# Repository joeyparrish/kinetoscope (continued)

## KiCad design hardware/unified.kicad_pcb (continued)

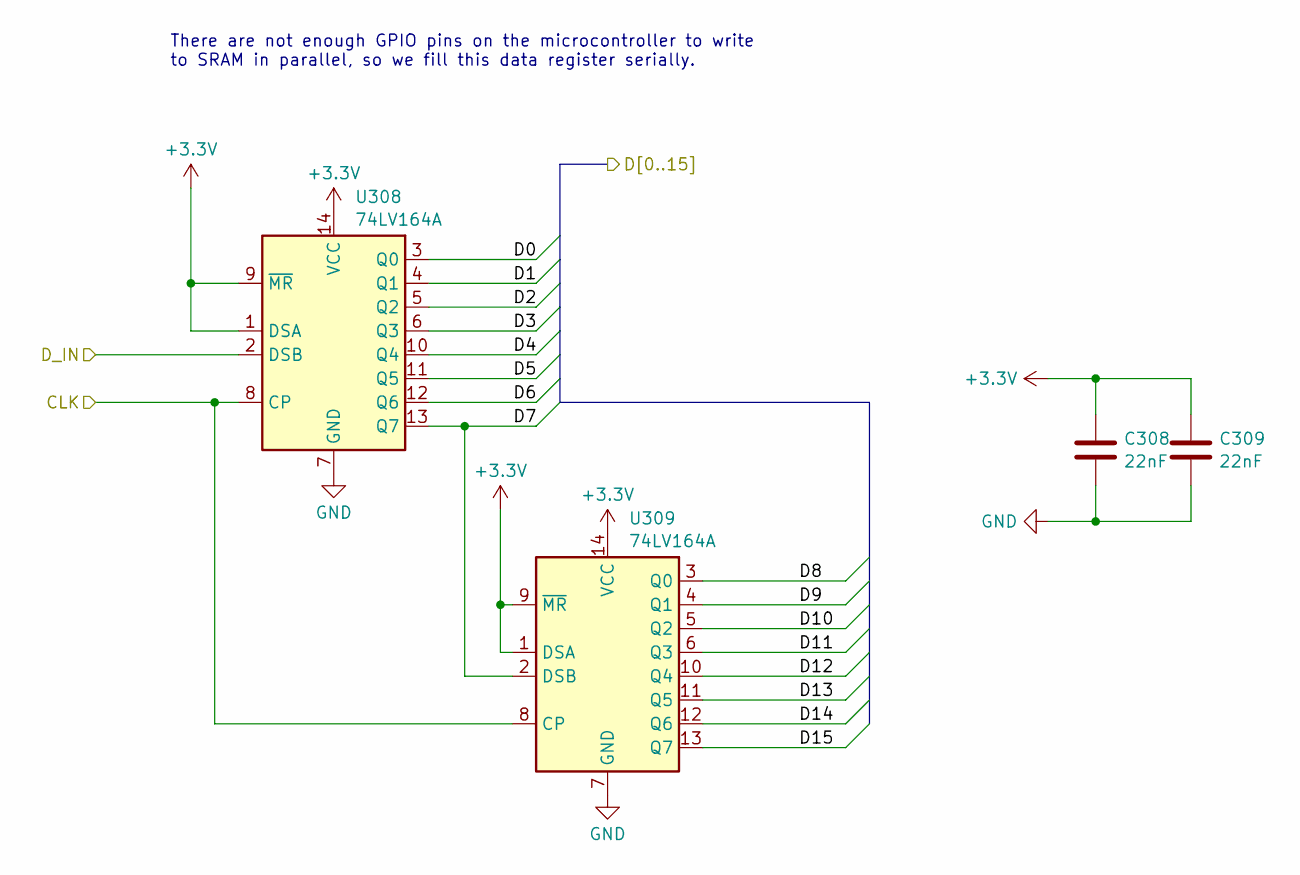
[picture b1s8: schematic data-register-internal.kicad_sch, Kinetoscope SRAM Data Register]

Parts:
C308, C309: 22nF; C_0603_1608Metric; Mouser Part Number 187-CL10B223KB8NNNC
U308, U309: 74LV164A; TSSOP-14_4.4x5mm_P0.65mm; Mouser Part Number 595-SN74LV164APWR

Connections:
+3.3V: C308.1, C309.1, U308.1 (DSA), U308.9 (~MR), U308.14 (VCC), U309.1 (DSA), U309.9 (~MR), U309.14 (VCC); also elsewhere on the board
GND: C308.2, C309.2, U308.7 (GND), U309.7 (GND); also elsewhere on the board
SRAM_D_CLK: U308.8 (CP), U309.8 (CP); also elsewhere on the board
SRAM_D_IN0: U308.3 (Q0); also elsewhere on the board
SRAM_D_IN1: U308.4 (Q1); also elsewhere on the board
SRAM_D_IN2: U308.5 (Q2); also elsewhere on the board
SRAM_D_IN3: U308.6 (Q3); also elsewhere on the board
SRAM_D_IN4: U308.10 (Q4); also elsewhere on the board
SRAM_D_IN5: U308.11 (Q5); also elsewhere on the board
SRAM_D_IN6: U308.12 (Q6); also elsewhere on the board
SRAM_D_IN7: U308.13 (Q7), U309.2 (DSB); also elsewhere on the board
SRAM_D_IN8: U309.3 (Q0); also elsewhere on the board
SRAM_D_IN9: U309.4 (Q1); also elsewhere on the board
SRAM_D_IN10: U309.5 (Q2); also elsewhere on the board
SRAM_D_IN11: U309.6 (Q3); also elsewhere on the board
SRAM_D_IN12: U309.10 (Q4); also elsewhere on the board
SRAM_D_IN13: U309.11 (Q5); also elsewhere on the board
SRAM_D_IN14: U309.12 (Q6); also elsewhere on the board
SRAM_D_IN15: U309.13 (Q7); also elsewhere on the board
SRAM_D_NEXT: U308.2 (DSB); also elsewhere on the board

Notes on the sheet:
There are not enough GPIO pins on the microcontroller to write to SRAM in parallel, so we fill this data register serially.

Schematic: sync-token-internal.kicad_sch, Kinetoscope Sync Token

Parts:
C310, C311: 22nF; C_0603_1608Metric; Mouser Part Number 187-CL10B223KB8NNNC
U310: 74AHC74; TSSOP-14_4.4x5mm_P0.65mm; Mouser Part Number 595-SN74AHC74PWR
U311: 74LVC2G125; VSSOP-8_2.3x2mm_P0.5mm; Mouser Part Number 771-LVC2G125DC125; JLCPCB Part Number C548582

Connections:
+3.3V: C310.1, C311.1, U310.14 (VCC), U311.8 (VCC); also elsewhere on the board
/microcontroller-internal/CMD_3V: U310.5 (Q), U311.2; also elsewhere on the board
/microcontroller-internal/ERR_3V: U310.9 (Q), U311.5; also elsewhere on the board
/microcontroller-internal/~CMD_CLR: U310.1 (~R); also elsewhere on the board
/microcontroller-internal/~CMD_OE: U311.1; also elsewhere on the board
/microcontroller-internal/~CMD_SET: U310.4 (~S); also elsewhere on the board
/microcontroller-internal/~ERR_CLR: U310.13 (~R); also elsewhere on the board
/microcontroller-internal/~ERR_OE: U311.7; also elsewhere on the board
/microcontroller-internal/~ERR_SET: U310.10 (~S); also elsewhere on the board
GND: C310.2, C311.2, U310.2 (D), U310.3 (C), U310.7 (GND), U310.11 (C), U310.12 (D), U311.4 (GND); also elsewhere on the board
SEGA_D0: U311.3, U311.6; also elsewhere on the board

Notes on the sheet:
Always on, outputs at 3.3V to the microcontroller.
Controlled by ~{ERR_OE}, outputs at 3.3V (OK) to M68k on the shared data bus. ~{ERR_OE} and ~{CMD_OE} must be mutually exclusive.
These are synchronization tokens between the M68k and the microcontroller. The tokens will be cleared on boot/reset. The M68k will be able to set the command token (~{CMD_SET}), indicating to the microcontroller that a command is ready to be executed. The microcontroller will be able to clear the c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
Controlled by ~{CMD_OE}, outputs at 3.3V (OK) to M68k on the shared data bus. ~{ERR_OE} and ~{CMD_OE} must be mutually exclusive.

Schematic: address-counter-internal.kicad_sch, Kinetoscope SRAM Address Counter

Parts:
C303, C304, C305, C306, C307: 22nF; C_0603_1608Metric; Mouser Part Number 187-CL10B223KB8NNNC
U303, U304, U305, U306, U307: 74LV161A; TSSOP-16_4.4x5mm_P0.65mm; Mouser Part Number 595-SN74LV161APWR

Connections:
+3.3V: C303.1, C304.1, C305.1, C306.1, C307.1, U303.3 (D0), U303.4 (D1), U303.5 (D2), U303.6 (D3), U303.7 (CEP), U303.9 (~PE), U303.10 (CET), U303.16 (VCC), U304.3 (D0), U304.4 (D1), U304.5 (D2), U304.6 (D3), U304.7 (CEP), U304.9 (~PE), U304.16 (VCC), U305.3 (D0), U305.4 (D1), U305.5 (D2), U305.6 (D3), U305.7 (CEP), U305.9 (~PE), U305.16 (VCC), U306.3 (D0), U306.4 (D1), U306.5 (D2), U306.6 (D3), U306.7 (CEP), U306.9 (~PE), U306.16 (VCC), U307.3 (D0), U307.4 (D1), U307.5 (D2), U307.6 (D3), U307.7 (CEP), U307.9 (~PE), U307.16 (VCC); also elsewhere on the board
/microcontroller-internal/address-counter-internal/AR0: U303.15 (TC), U304.10 (CET)
/microcontroller-internal/address-counter-internal/AR1: U304.15 (TC), U305.10 (CET)
/microcontroller-internal/address-counter-internal/AR2: U305.15 (TC), U306.10 (CET)
/microcontroller-internal/address-counter-internal/AR3: U306.15 (TC), U307.10 (CET)
GND: C303.2, C304.2, C305.2, C306.2, C307.2, U303.8 (GND), U304.8 (GND), U305.8 (GND), U306.8 (GND), U307.8 (GND); also elsewhere on the board
SRAM_W_A0: U303.14 (Q0); also elsewhere on the board
SRAM_W_A1: U303.13 (Q1); also elsewhere on the board
SRAM_W_A2: U303.12 (Q2); also elsewhere on the board
SRAM_W_A3: U303.11 (Q3); also elsewhere on the board
SRAM_W_A4: U304.14 (Q0); also elsewhere on the board
SRAM_W_A5: U304.13 (Q1); also elsewhere on the board
SRAM_W_A6: U304.12 (Q2); also elsewhere on the board
SRAM_W_A7: U304.11 (Q3); also elsewhere on the board
SRAM_W_A8: U305.14 (Q0); also elsewhere on the board
SRAM_W_A9: U305.13 (Q1); also elsewhere on the board
SRAM_W_A10: U305.12 (Q2); also elsewhere on the board
SRAM_W_A11: U305.11 (Q3); also elsewhere on the board
SRAM_W_A12: U306.14 (Q0); also elsewhere on the board
SRAM_W_A13: U306.13 (Q1); also elsewhere on the board
SRAM_W_A14: U306.12 (Q2); also elsewhere on the board
SRAM_W_A15: U306.11 (Q3); also elsewhere on the board
SRAM_W_A16: U307.14 (Q0); also elsewhere on the board
SRAM_W_A17: U307.13 (Q1); also elsewhere on the board
SRAM_W_A18: U307.12 (Q2); also elsewhere on the board
SRAM_W_A_CLK: U303.2 (CP), U304.2 (CP), U305.2 (CP), U306.2 (CP), U307.2 (CP); also elsewhere on the board
~SRAM_W_A_CLR: U303.1 (~MR), U304.1 (~MR), U305.1 (~MR), U306.1 (~MR), U307.1 (~MR); also elsewhere on the board

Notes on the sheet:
There are not enough GPIO pins on the microcontroller to write to SRAM in parallel, so we increment this counter for the SRAM address.
These run on 3V, and output 3V logic, but tolerate 5V input.

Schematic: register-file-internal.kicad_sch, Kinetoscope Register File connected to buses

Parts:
C312, C313, C314: 22nF; C_0603_1608Metric; Mouser Part Number 187-CL10B223KB8NNNC
U312: 74AHC04; TSSOP-14_4.4x5mm_P0.65mm; Mouser Part Number 595-SN74AHC04PWR; JLCPCB Part Number C415550
U313, U314: 74AHC373; TSSOP-20_4.4x6.5mm_P0.65mm; Mouser Part Number 595-SN74AHC373PWR; JLCPCB Part Number C80242

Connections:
+3.3V: C312.1, C313.1, C314.1, U312.14 (VCC), U313.20 (VCC), U314.20 (VCC); also elsewhere on the board
/microcontroller-internal/REG_R_D0: U313.2 (O0), U314.2 (O0); also elsewhere on the board
/microcontroller-internal/REG_R_D1: U313.5 (O1), U314.5 (O1); also elsewhere on the board
/microcontroller-internal/REG_R_D2: U313.6 (O2), U314.6 (O2); also elsewhere on the board
/microcontroller-internal/REG_R_D3: U313.9 (O3), U314.9 (O3); also elsewhere on the board
/microcontroller-internal/REG_R_D4: U313.12 (O4), U314.12 (O4); also elsewhere on the board
/microcontroller-internal/REG_R_D5: U313.15 (O5), U314.15 (O5); also elsewhere on the board
/microcontroller-internal/REG_R_D6: U313.16 (O6), U314.16 (O6); also elsewhere on the board
/microcontroller-internal/REG_R_D7: U313.19 (O7), U314.19 (O7); also elsewhere on the board
/microcontroller-internal/register-file-internal/REG_0_WE: U312.2, U313.11 (LE)
/microcontroller-internal/register-file-internal/REG_1_WE: U312.4, U314.11 (LE)
/microcontroller-internal/~REG_0_OE: U313.1 (OE); also elsewhere on the board
/microcontroller-internal/~REG_0_WE: U312.1; also elsewhere on the board
/microcontroller-internal/~REG_1_OE: U314.1 (OE); also elsewhere on the board
/microcontroller-internal/~REG_1_WE: U312.3; also elsewhere on the board
GND: C312.2, C313.2, C314.2, U312.5, U312.7 (GND), U312.9, U312.11, U312.13, U313.10 (GND), U314.10 (GND); also elsewhere on the board
SEGA_D0: U313.3 (D0), U314.3 (D0); also elsewhere on the board
SEGA_D1: U313.4 (D1), U314.4 (D1); also elsewhere on the board
SEGA_D2: U313.7 (D2), U314.7 (D2); also elsewhere on the board
SEGA_D3: U313.8 (D3), U314.8 (D3); also elsewhere on the board
SEGA_D4: U313.13 (D4), U314.13 (D4); also elsewhere on the board
SEGA_D5: U313.14 (D5), U314.14 (D5); also elsewhere on the board
SEGA_D6: U313.17 (D6), U314.17 (D6); also elsewhere on the board
SEGA_D7: U313.18 (D7), U314.18 (D7); also elsewhere on the board

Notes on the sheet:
This is a pair of 8-bit registers that can be independently read and written by the two processors (one reads, one writes). The registers are assumed to written from the Sega's shared data bus and read by the microcontroller. Each register has its own write-enable and read-enable, but only one regi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
3V signals
These are unused gates.
The write-enable signals from our address decoder are active-low, but the latch signal here is active-high. Hence the inverter.
5V signals

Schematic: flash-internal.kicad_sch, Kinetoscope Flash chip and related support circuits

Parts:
C5, C6, C7, C8, C9, C10, C11, C12, C13, C14, C15: 22nF; C_0603_1608Metric; Mouser Part Number 80-C0603C223K4R
U3, U4, U5, U7, U8: 74LVC8T245; TSSOP-24_4.4x7.8mm_P0.65mm; Mouser Part Number 595-SN74LVC8T245PWR
U6: S29AL016J55TFIR20; TSOP-I-48_18.4x12mm_P0.5mm; Mouser Part Number 797-S29AL016J55TFIR2

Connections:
+3.3V: C5.1, C6.1, C7.1, C8.1, C9.1, C10.1, C11.1, C12.1, C13.1, C14.1, C15.1, U3.1 (V_{CCA}), U3.2 (DIR), U3.23 (V_{CCB}), U3.24 (V_{CCB}), U4.1 (V_{CCA}), U4.2 (DIR), U4.23 (V_{CCB}), U4.24 (V_{CCB}), U5.1 (V_{CCA}), U5.2 (DIR), U5.23 (V_{CCB}), U5.24 (V_{CCB}), U6.14 (~WP), U6.37 (VCC), U6.47 (~BYTE), U7.1 (V_{CCA}), U7.23 (V_{CCB}), U7.24 (V_{CCB}), U8.1 (V_{CCA}), U8.23 (V_{CCB}), U8.24 (V_{CCB}); also elsewhere on the board
/cart-internal/flash-internal/A0_3V: U3.21 (B1), U6.25 (A0)
/cart-internal/flash-internal/A1_3V: U3.20 (B2), U6.24 (A1)
/cart-internal/flash-internal/A2_3V: U3.19 (B3), U6.23 (A2)
/cart-internal/flash-internal/A3_3V: U3.18 (B4), U6.22 (A3)
/cart-internal/flash-internal/A4_3V: U3.17 (B5), U6.21 (A4)
/cart-internal/flash-internal/A5_3V: U3.16 (B6), U6.20 (A5)
/cart-internal/flash-internal/A6_3V: U3.15 (B7), U6.19 (A6)
/cart-internal/flash-internal/A7_3V: U3.14 (B8), U6.18 (A7)
/cart-internal/flash-internal/A8_3V: U4.21 (B1), U6.8 (A8)
/cart-internal/flash-internal/A9_3V: U4.20 (B2), U6.7 (A9)
/cart-internal/flash-internal/A10_3V: U4.19 (B3), U6.6 (A10)
/cart-internal/flash-internal/A11_3V: U4.18 (B4), U6.5 (A11)
/cart-internal/flash-internal/A12_3V: U4.17 (B5), U6.4 (A12)
/cart-internal/flash-internal/A13_3V: U4.16 (B6), U6.3 (A13)
/cart-internal/flash-internal/A14_3V: U4.15 (B7), U6.2 (A14)
/cart-internal/flash-internal/A15_3V: U4.14 (B8), U6.1 (A15)
/cart-internal/flash-internal/A16_3V: U5.21 (B1), U6.48 (A16)
/cart-internal/flash-internal/A17_3V: U5.20 (B2), U6.17 (A17)
/cart-internal/flash-internal/A18_3V: U5.19 (B3), U6.16 (A18)
/cart-internal/flash-internal/A19_3V: U5.18 (B4), U6.9 (A19)
/cart-internal/flash-internal/D0_3V: U6.29 (DQ0), U7.3 (A1)
/cart-internal/flash-internal/D1_3V: U6.31 (DQ1), U7.4 (A2)
/cart-internal/flash-internal/D2_3V: U6.33 (DQ2), U7.5 (A3)
/cart-internal/flash-internal/D3_3V: U6.35 (DQ3), U7.6 (A4)
/cart-internal/flash-internal/D4_3V: U6.38 (DQ4), U7.7 (A5)
/cart-internal/flash-internal/D5_3V: U6.40 (DQ5), U7.8 (A6)
/cart-internal/flash-internal/D6_3V: U6.42 (DQ6), U7.9 (A7)
/cart-internal/flash-internal/D7_3V: U6.44 (DQ7), U7.10 (A8)
/cart-internal/flash-internal/D8_3V: U6.30 (DQ8), U8.3 (A1)
/cart-internal/flash-internal/D9_3V: U6.32 (DQ9), U8.4 (A2)
/cart-internal/flash-internal/D10_3V: U6.34 (DQ10), U8.5 (A3)
/cart-internal/flash-internal/D11_3V: U6.36 (DQ11), U8.6 (A4)
/cart-internal/flash-internal/D12_3V: U6.39 (DQ12), U8.7 (A5)
/cart-internal/flash-internal/D13_3V: U6.41 (DQ13), U8.8 (A6)
/cart-internal/flash-internal/D14_3V: U6.43 (DQ14), U8.9 (A7)
/cart-internal/flash-internal/D15_3V: U6.45 (DQ15/A-1), U8.10 (A8)
/cart-internal/flash-internal/~OE_3V: U5.14 (B8), U6.28 (~OE)
/cart-internal/flash-internal/~RESET_3V: U5.17 (B5), U6.12 (~RESET)
/cart-internal/flash-internal/~WE_3V: U5.16 (B6), U6.11 (~WE), U7.2 (DIR), U8.2 (DIR)
/cart-internal/~FLASH_CE: U6.26 (~CE), U7.22 (~OE), U8.22 (~OE); also elsewhere on the board
GND: C5.2, C6.2, C7.2, C8.2, C9.2, C10.2, C11.2, C12.2, C13.2, C14.2, C15.2, U3.11 (GND), U3.12 (GND), U3.13 (GND), U3.22 (~OE), U4.11 (GND), U4.12 (GND), U4.13 (GND), U4.22 (~OE), U5.9 (A7), U5.11 (GND), U5.12 (GND), U5.13 (GND), U5.22 (~OE), U6.27 (VSS1), U6.46 (VSS2), U7.11 (GND), U7.12 (GND), U7.13 (GND), U8.11 (GND), U8.12 (GND), U8.13 (GND); also elsewhere on the board
SEGA_A1: U3.3 (A1); also elsewhere on the board
SEGA_A2: U3.4 (A2); also elsewhere on the board
SEGA_A3: U3.5 (A3); also elsewhere on the board
SEGA_A4: U3.6 (A4); also elsewhere on the board
SEGA_A5: U3.7 (A5); also elsewhere on the board
SEGA_A6: U3.8 (A6); also elsewhere on the board
SEGA_A7: U3.9 (A7); also elsewhere on the board
SEGA_A8: U3.10 (A8); also elsewhere on the board
SEGA_A9: U4.3 (A1); also elsewhere on the board
SEGA_A10: U4.4 (A2); also elsewhere on the board
SEGA_A11: U4.5 (A3); also elsewhere on the board
SEGA_A12: U4.6 (A4); also elsewhere on the board
SEGA_A13: U4.7 (A5); also elsewhere on the board
SEGA_A14: U4.8 (A6); also elsewhere on the board
SEGA_A15: U4.9 (A7); also elsewhere on the board
SEGA_A16: U4.10 (A8); also elsewhere on the board
SEGA_A17: U5.3 (A1); also elsewhere on the board
SEGA_A18: U5.4 (A2); also elsewhere on the board
SEGA_A19: U5.5 (A3); also elsewhere on the board
SEGA_A20: U5.6 (A4); also elsewhere on the board
SEGA_D0: U7.21 (B1); also elsewhere on the board
SEGA_D1: U7.20 (B2); also elsewhere on the board
SEGA_D2: U7.19 (B3); also elsewhere on the board
SEGA_D3: U7.18 (B4); also elsewhere on the board
SEGA_D4: U7.17 (B5); also elsewhere on the board
SEGA_D5: U7.16 (B6); also elsewhere on the board
SEGA_D6: U7.15 (B7); also elsewhere on the board
SEGA_D7: U7.14 (B8); also elsewhere on the board
SEGA_D8: U8.21 (B1); also elsewhere on the board
SEGA_D9: U8.20 (B2); also elsewhere on the board
SEGA_D10: U8.19 (B3); also elsewhere on the board
SEGA_D11: U8.18 (B4); also elsewhere on the board
SEGA_D12: U8.17 (B5); also elsewhere on the board
SEGA_D13: U8.16 (B6); also elsewhere on the board
SEGA_D14: U8.15 (B7); also elsewhere on the board
SEGA_D15: U8.14 (B8); also elsewhere on the board
~SEGA_OE: U5.10 (A8); also elsewhere on the board
~SEGA_RESET: U5.7 (A5); also elsewhere on the board
~SEGA_WE_LB: U5.8 (A6); also elsewhere on the board

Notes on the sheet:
DIR is high, data always flows A => B.
This outputs at 3.3V logic levels, which are compatible with the Sega's 5V TTL system. We rely on this fact so that the cart can remain compatible with both the Sega and the FlashKit programmer. If we made the right side 5V, then the minimum high level for data input would be 3.5V (VccB * 0.7), whi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
~{OE} is connected to ~{CE_3V}. Throughput (in either direction) will be enabled any time the address space indicates reading or writing flash (0-2MB).
This is where the cartridge "ROM" image is stored. Not an actual ROM, or EPROM, but Flash RAM, which is way cheaper. Maximum ROM size is 2MB. The flash chip is compatible with the Krikzz Flashkit MD Programmer. This chip gets its own voltage regulator so that this base cartridge board can be progra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
DIR is high to pass data from A to B. DIR is connected to ~{WE_3V}. ~{WE_3V} is high when we're reading. Therefore the reading side (flash chip side) should be A.

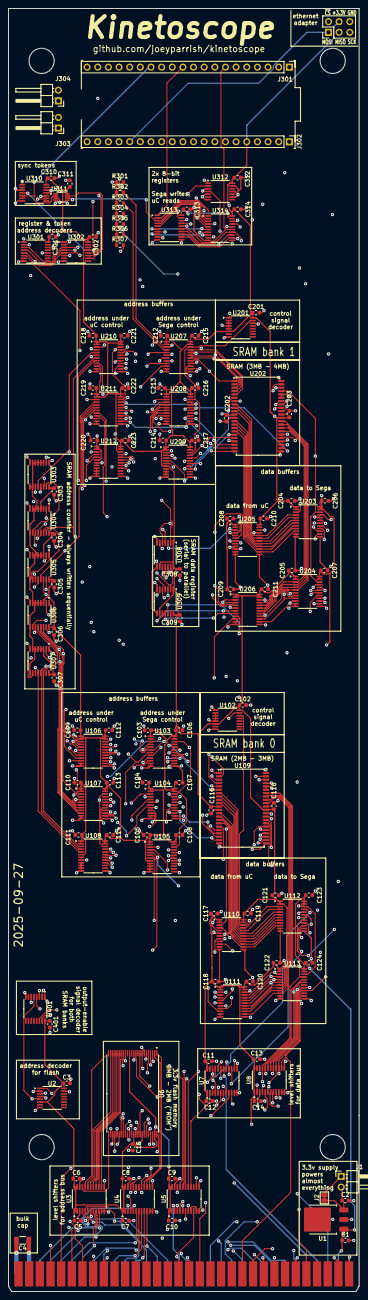
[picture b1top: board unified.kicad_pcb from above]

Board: 4 copper layers, 83.7 x 306.2 mm, 141 parts (0 on the bottom side), 245 nets.

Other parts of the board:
P9, P10: (no value)

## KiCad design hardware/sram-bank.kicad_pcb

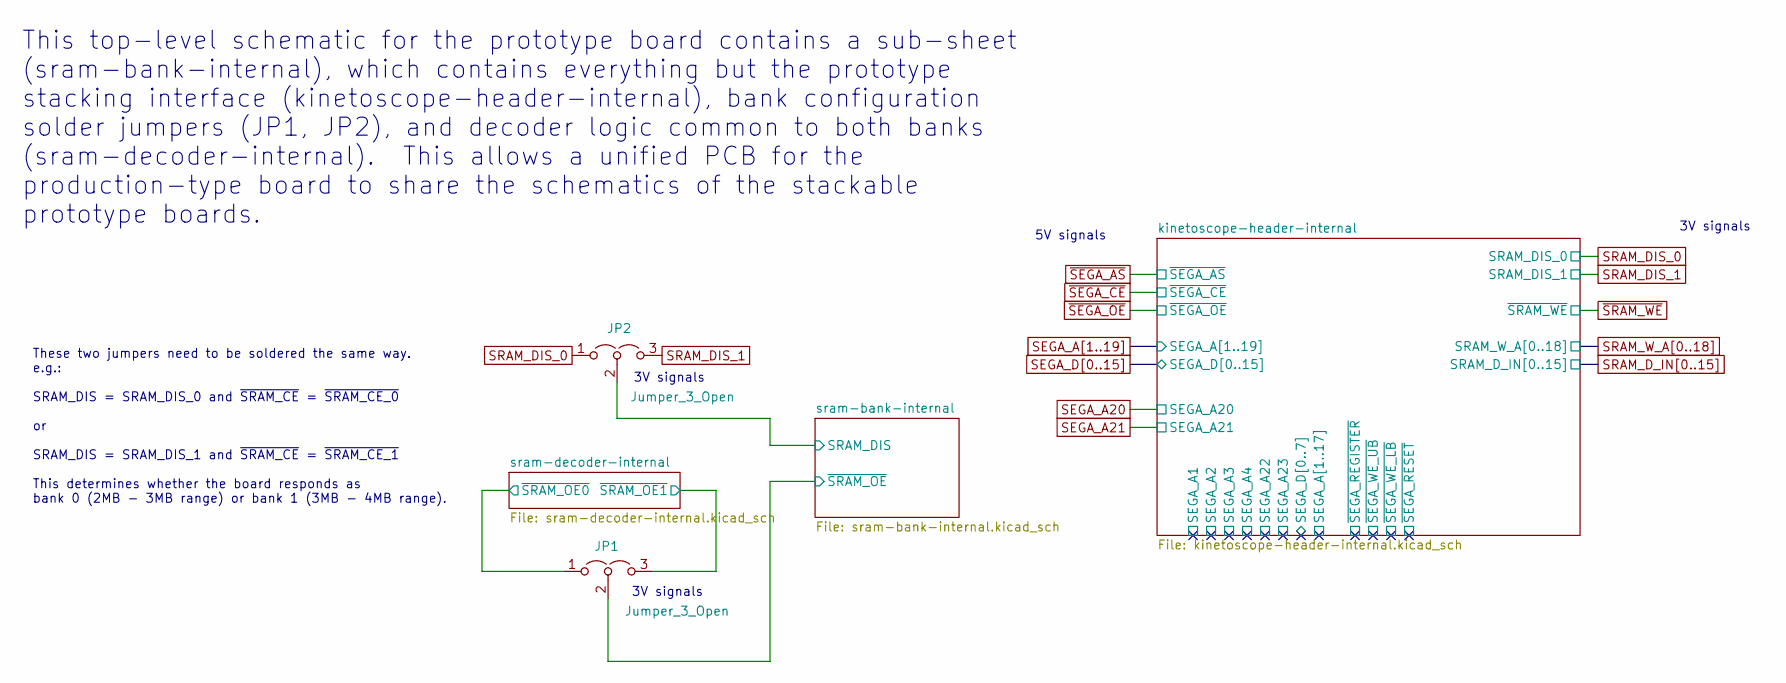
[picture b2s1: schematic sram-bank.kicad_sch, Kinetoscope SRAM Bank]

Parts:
JP1, JP2: Jumper_3_Open; SolderJumper-3_P1.3mm_Open_RoundedPad1.0x1.5mm_NumberLabels

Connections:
/sram-bank-internal/SRAM_DIS: JP2.2 (C); also elsewhere on the board
/sram-bank-internal/~SRAM_OE: JP1.2 (C); also elsewhere on the board
/sram-decoder-internal/~SRAM_OE0: JP1.1 (A); also elsewhere on the board
/sram-decoder-internal/~SRAM_OE1: JP1.3 (B); also elsewhere on the board
SRAM_DIS_0: JP2.1 (A); also elsewhere on the board
SRAM_DIS_1: JP2.3 (B); also elsewhere on the board

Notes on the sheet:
This top-level schematic for the prototype board contains a sub-sheet (sram-bank-internal), which contains everything but the prototype stacking interface (kinetoscope-header-internal), bank configuration solder jumpers (JP1, JP2), and decoder logic common to both banks (sram-decoder-internal). Thi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
5V signals
These two jumpers need to be soldered the same way. e.g.: SRAM_DIS = SRAM_DIS_0 and ~{SRAM_CE} = ~{SRAM_CE_0} or SRAM_DIS = SRAM_DIS_1 and ~{SRAM_CE} = ~{SRAM_CE_1} This determines whether the board responds as bank 0 (2MB - 3MB range) or bank 1 (3MB - 4MB range).
3V signals

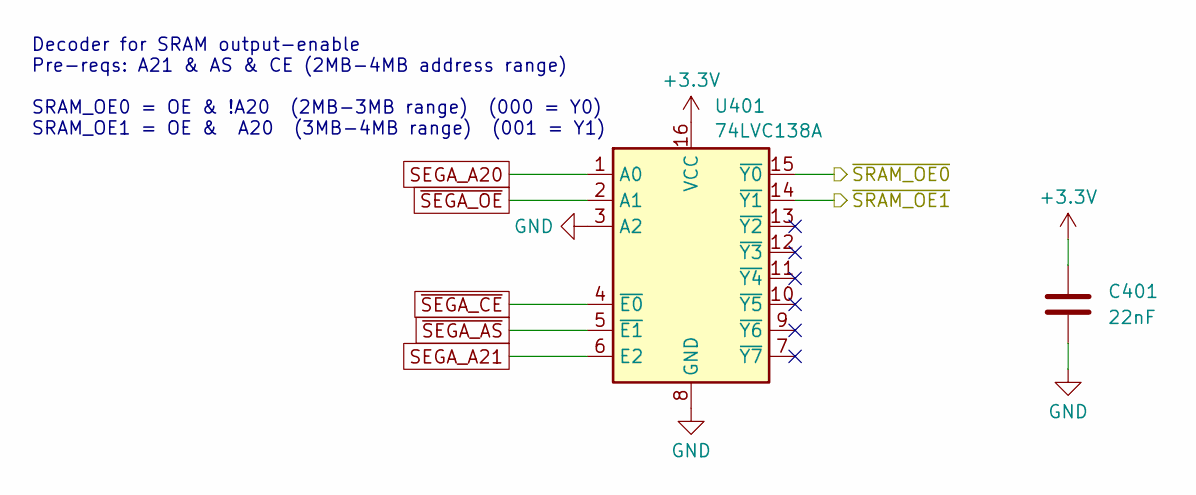
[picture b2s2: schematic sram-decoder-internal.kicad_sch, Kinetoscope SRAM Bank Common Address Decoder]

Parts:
C401: 22nF; C_0603_1608Metric; Mouser Part Number 80-C0603C223K4R; JLCPCB Part Number CL10B223KB8NNNC
U401: 74LVC138A; TSSOP-16_4.4x5mm_P0.65mm; Mouser Part Number 771-74LVC138APW-T; JLCPCB Part Number C6062

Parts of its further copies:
C1: 22nF; C_0603_1608Metric; Mouser Part Number 80-C0603C223K4R; JLCPCB Part Number CL10B223KB8NNNC
U1: 74LVC138A; TSSOP-16_4.4x5mm_P0.65mm; Mouser Part Number 771-74LVC138APW-T; JLCPCB Part Number C6062

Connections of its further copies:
+3.3V: C1.1, U1.16 (VCC); also elsewhere on the board
/sram-decoder-internal/~SRAM_OE0: U1.15 (~Y0); also elsewhere on the board
/sram-decoder-internal/~SRAM_OE1: U1.14 (~Y1); also elsewhere on the board
GND: C1.2, U1.3 (A2), U1.8 (GND); also elsewhere on the board
SEGA_A20: U1.1 (A0); also elsewhere on the board
SEGA_A21: U1.6 (E2); also elsewhere on the board
~SEGA_AS: U1.5 (~E1); also elsewhere on the board
~SEGA_CE: U1.4 (~E0); also elsewhere on the board
~SEGA_OE: U1.2 (A1); also elsewhere on the board

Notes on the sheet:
Decoder for SRAM output-enable Pre-reqs: A21 & AS & CE (2MB-4MB address range) SRAM_OE0 = OE & !A20 (2MB-3MB range) (000 = Y0) SRAM_OE1 = OE & A20 (3MB-4MB range) (001 = Y1)

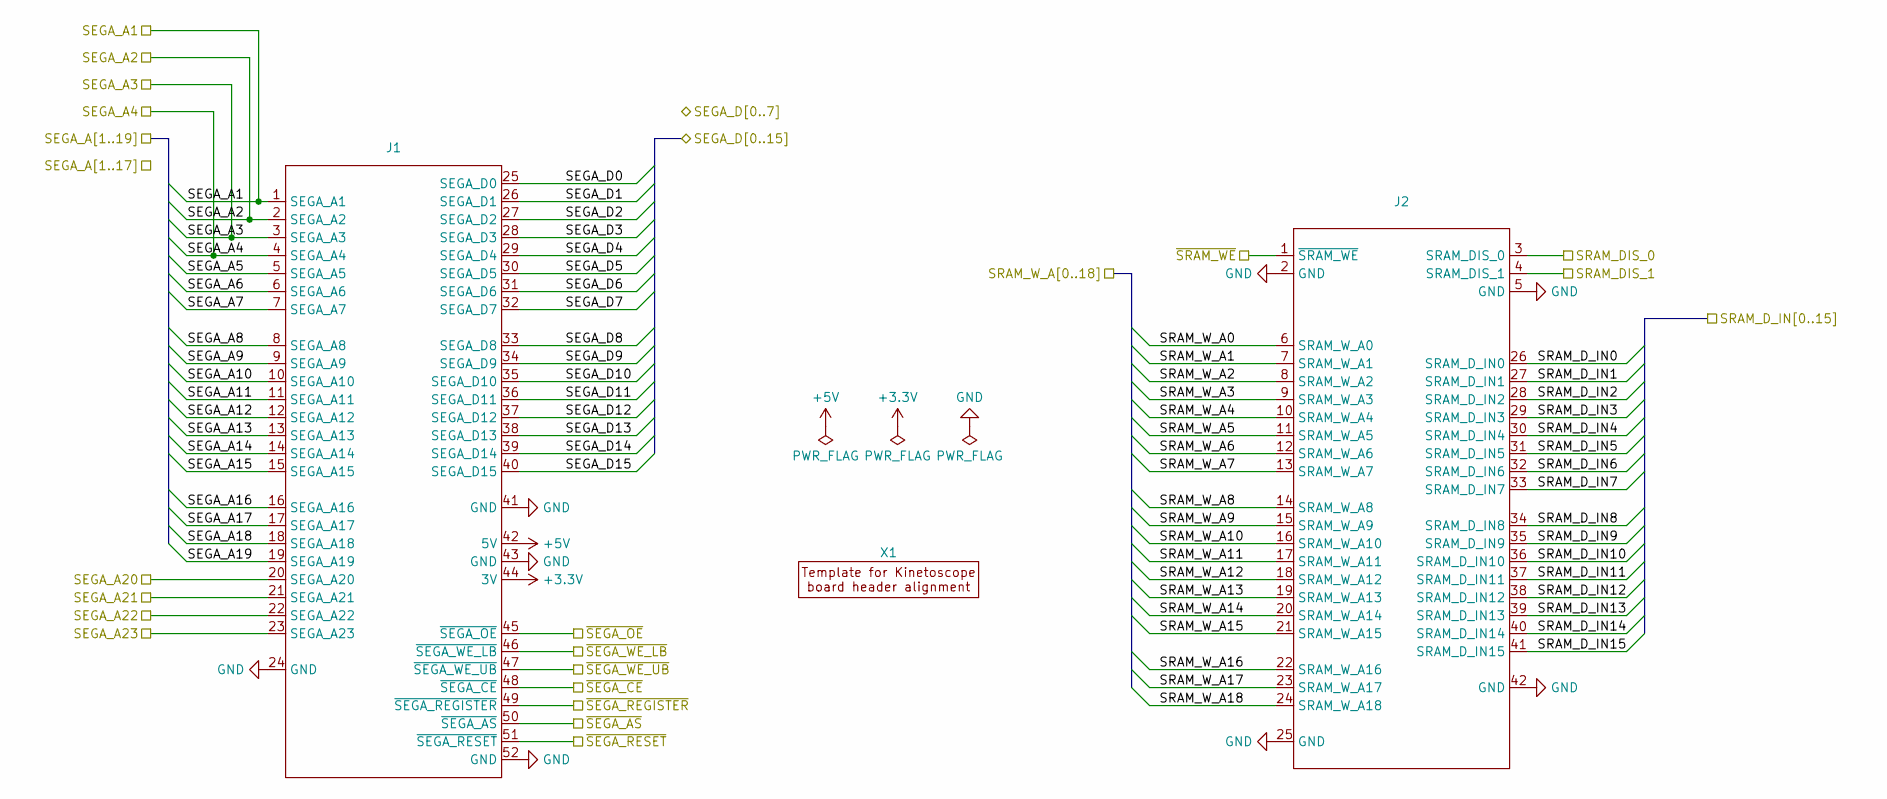
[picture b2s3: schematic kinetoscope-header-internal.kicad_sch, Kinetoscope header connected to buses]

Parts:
J1: PinHeader_2x26_P2.54mm_Vertical
J2: PinHeader_2x21_P2.54mm_Vertical
X1: kinetoscope-cart-board-template

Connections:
+3.3V: J1.44 (3V); also elsewhere on the board
+5V: J1.42 (5V); also elsewhere on the board
/kinetoscope-header-internal/SEGA_A22: J1.22 (SEGA_A22)
/kinetoscope-header-internal/SEGA_A23: J1.23 (SEGA_A23)
/kinetoscope-header-internal/~SEGA_REGISTER: J1.49 (~SEGA_REGISTER)
/kinetoscope-header-internal/~SEGA_RESET: J1.51 (~SEGA_RESET)
/kinetoscope-header-internal/~SEGA_WE_LB: J1.46 (~SEGA_WE_LB)
/kinetoscope-header-internal/~SEGA_WE_UB: J1.47 (~SEGA_WE_UB)
GND: J1.24 (GND), J1.41 (GND), J1.43 (GND), J1.52 (GND), J2.2 (GND), J2.5 (GND), J2.25 (GND), J2.42 (GND); also elsewhere on the board
SEGA_A1: J1.1 (SEGA_A1); also elsewhere on the board
SEGA_A2: J1.2 (SEGA_A2); also elsewhere on the board
SEGA_A3: J1.3 (SEGA_A3); also elsewhere on the board
SEGA_A4: J1.4 (SEGA_A4); also elsewhere on the board
SEGA_A5: J1.5 (SEGA_A5); also elsewhere on the board
SEGA_A6: J1.6 (SEGA_A6); also elsewhere on the board
SEGA_A7: J1.7 (SEGA_A7); also elsewhere on the board
SEGA_A8: J1.8 (SEGA_A8); also elsewhere on the board
SEGA_A9: J1.9 (SEGA_A9); also elsewhere on the board
SEGA_A10: J1.10 (SEGA_A10); also elsewhere on the board
SEGA_A11: J1.11 (SEGA_A11); also elsewhere on the board
SEGA_A12: J1.12 (SEGA_A12); also elsewhere on the board
SEGA_A13: J1.13 (SEGA_A13); also elsewhere on the board
SEGA_A14: J1.14 (SEGA_A14); also elsewhere on the board
SEGA_A15: J1.15 (SEGA_A15); also elsewhere on the board
SEGA_A16: J1.16 (SEGA_A16); also elsewhere on the board
SEGA_A17: J1.17 (SEGA_A17); also elsewhere on the board
SEGA_A18: J1.18 (SEGA_A18); also elsewhere on the board
SEGA_A19: J1.19 (SEGA_A19); also elsewhere on the board
SEGA_A20: J1.20 (SEGA_A20); also elsewhere on the board
SEGA_A21: J1.21 (SEGA_A21); also elsewhere on the board
SEGA_D0: J1.25 (SEGA_D0); also elsewhere on the board
SEGA_D1: J1.26 (SEGA_D1); also elsewhere on the board
SEGA_D2: J1.27 (SEGA_D2); also elsewhere on the board
SEGA_D3: J1.28 (SEGA_D3); also elsewhere on the board
SEGA_D4: J1.29 (SEGA_D4); also elsewhere on the board
SEGA_D5: J1.30 (SEGA_D5); also elsewhere on the board
SEGA_D6: J1.31 (SEGA_D6); also elsewhere on the board
SEGA_D7: J1.32 (SEGA_D7); also elsewhere on the board
SEGA_D8: J1.33 (SEGA_D8); also elsewhere on the board
SEGA_D9: J1.34 (SEGA_D9); also elsewhere on the board
SEGA_D10: J1.35 (SEGA_D10); also elsewhere on the board
SEGA_D11: J1.36 (SEGA_D11); also elsewhere on the board
SEGA_D12: J1.37 (SEGA_D12); also elsewhere on the board
SEGA_D13: J1.38 (SEGA_D13); also elsewhere on the board
SEGA_D14: J1.39 (SEGA_D14); also elsewhere on the board
SEGA_D15: J1.40 (SEGA_D15); also elsewhere on the board
SRAM_DIS_0: J2.3 (SRAM_DIS_0); also elsewhere on the board
SRAM_DIS_1: J2.4 (SRAM_DIS_1); also elsewhere on the board
SRAM_D_IN0: J2.26 (SRAM_D_IN0); also elsewhere on the board
SRAM_D_IN1: J2.27 (SRAM_D_IN1); also elsewhere on the board
SRAM_D_IN2: J2.28 (SRAM_D_IN2); also elsewhere on the board
SRAM_D_IN3: J2.29 (SRAM_D_IN3); also elsewhere on the board
SRAM_D_IN4: J2.30 (SRAM_D_IN4); also elsewhere on the board
SRAM_D_IN5: J2.31 (SRAM_D_IN5); also elsewhere on the board
SRAM_D_IN6: J2.32 (SRAM_D_IN6); also elsewhere on the board
SRAM_D_IN7: J2.33 (SRAM_D_IN7); also elsewhere on the board
SRAM_D_IN8: J2.34 (SRAM_D_IN8); also elsewhere on the board
SRAM_D_IN9: J2.35 (SRAM_D_IN9); also elsewhere on the board
SRAM_D_IN10: J2.36 (SRAM_D_IN10); also elsewhere on the board
SRAM_D_IN11: J2.37 (SRAM_D_IN11); also elsewhere on the board
SRAM_D_IN12: J2.38 (SRAM_D_IN12); also elsewhere on the board
SRAM_D_IN13: J2.39 (SRAM_D_IN13); also elsewhere on the board
SRAM_D_IN14: J2.40 (SRAM_D_IN14); also elsewhere on the board
SRAM_D_IN15: J2.41 (SRAM_D_IN15); also elsewhere on the board
SRAM_W_A0: J2.6 (SRAM_W_A0); also elsewhere on the board
SRAM_W_A1: J2.7 (SRAM_W_A1); also elsewhere on the board
SRAM_W_A2: J2.8 (SRAM_W_A2); also elsewhere on the board
SRAM_W_A3: J2.9 (SRAM_W_A3); also elsewhere on the board
SRAM_W_A4: J2.10 (SRAM_W_A4); also elsewhere on the board
SRAM_W_A5: J2.11 (SRAM_W_A5); also elsewhere on the board
SRAM_W_A6: J2.12 (SRAM_W_A6); also elsewhere on the board
SRAM_W_A7: J2.13 (SRAM_W_A7); also elsewhere on the board
SRAM_W_A8: J2.14 (SRAM_W_A8); also elsewhere on the board
SRAM_W_A9: J2.15 (SRAM_W_A9); also elsewhere on the board
SRAM_W_A10: J2.16 (SRAM_W_A10); also elsewhere on the board
SRAM_W_A11: J2.17 (SRAM_W_A11); also elsewhere on the board
SRAM_W_A12: J2.18 (SRAM_W_A12); also elsewhere on the board
SRAM_W_A13: J2.19 (SRAM_W_A13); also elsewhere on the board
SRAM_W_A14: J2.20 (SRAM_W_A14); also elsewhere on the board
SRAM_W_A15: J2.21 (SRAM_W_A15); also elsewhere on the board
SRAM_W_A16: J2.22 (SRAM_W_A16); also elsewhere on the board
SRAM_W_A17: J2.23 (SRAM_W_A17); also elsewhere on the board
SRAM_W_A18: J2.24 (SRAM_W_A18); also elsewhere on the board
~SEGA_AS: J1.50 (~SEGA_AS); also elsewhere on the board
~SEGA_CE: J1.48 (~SEGA_CE); also elsewhere on the board
~SEGA_OE: J1.45 (~SEGA_OE); also elsewhere on the board
~SRAM_WE: J2.1 (~SRAM_WE); also elsewhere on the board

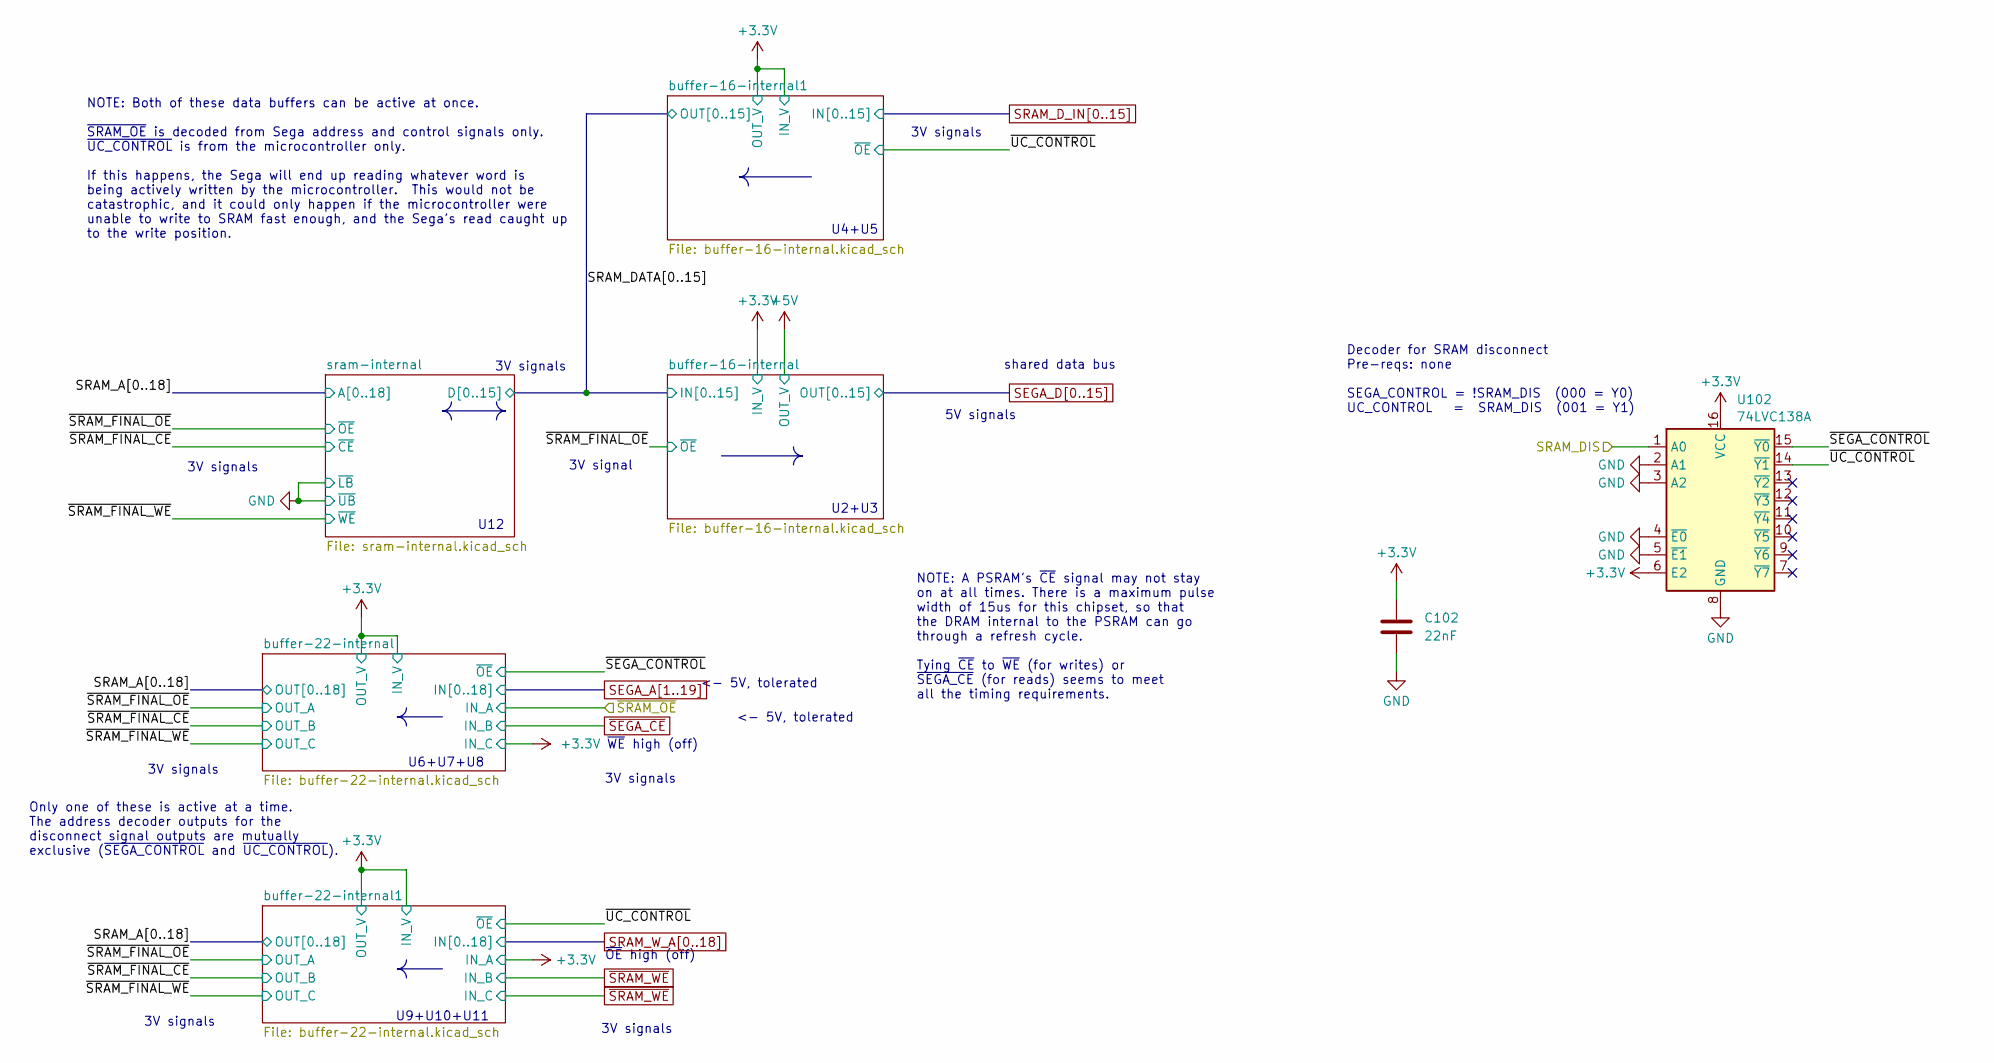
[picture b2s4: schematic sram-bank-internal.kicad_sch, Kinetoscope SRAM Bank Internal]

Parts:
C102: 22nF; C_0603_1608Metric; Mouser Part Number 80-C0603C223K4R; JLCPCB Part Number CL10B223KB8NNNC
U102: 74LVC138A; TSSOP-16_4.4x5mm_P0.65mm; Mouser Part Number 771-74LVC138APW-T; JLCPCB Part Number C6062

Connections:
+3.3V: C102.1, U102.6 (E2), U102.16 (VCC); also elsewhere on the board
/sram-bank-internal/SRAM_DIS: U102.1 (A0); also elsewhere on the board
/sram-bank-internal/~SEGA_CONTROL: U102.15 (~Y0); also elsewhere on the board
/sram-bank-internal/~UC_CONTROL: U102.14 (~Y1); also elsewhere on the board
GND: C102.2, U102.2 (A1), U102.3 (A2), U102.4 (~E0), U102.5 (~E1), U102.8 (GND); also elsewhere on the board

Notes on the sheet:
5V signals
U6+U7+U8
3V signals
U9+U10+U11
<- 5V, tolerated
U4+U5
U12
shared data bus
3V signal
Decoder for SRAM disconnect Pre-reqs: none SEGA_CONTROL = !SRAM_DIS (000 = Y0) UC_CONTROL = SRAM_DIS (001 = Y1)
NOTE: A PSRAM's ~{CE} signal may not stay on at all times. There is a maximum pulse width of 15us for this chipset, so that the DRAM internal to the PSRAM can go through a refresh cycle. Tying ~{CE} to ~{WE} (for writes) or ~{SEGA_CE} (for reads) seems to meet all the timing requirements.
~{OE} high (off)
U2+U3
Only one of these is active at a time. The address decoder outputs for the disconnect signal outputs are mutually exclusive (~{SEGA_CONTROL} and ~{UC_CONTROL}).
~{WE} high (off)
NOTE: Both of these data buffers can be active at once. ~{SRAM_OE} is decoded from Sega address and control signals only. ~{UC_CONTROL} is from the microcontroller only. If this happens, the Sega will end up reading whatever word is being actively written by the microcontroller. This would not be c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
